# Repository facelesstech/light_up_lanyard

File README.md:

# light_up_lanyard
light_up_lanyard

Blog post - https://facelesstech.wordpress.com/2023/03/04/light-up-paracord-lanyard/

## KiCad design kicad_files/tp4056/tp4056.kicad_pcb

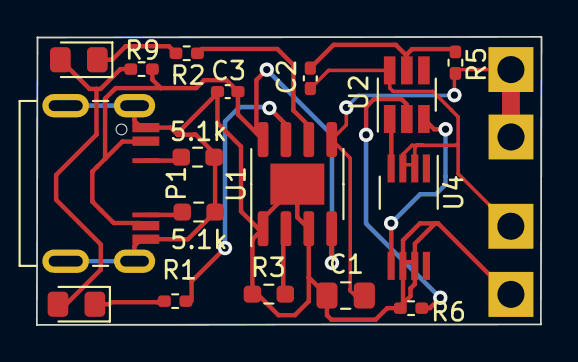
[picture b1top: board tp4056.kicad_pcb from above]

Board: 2 copper layers, 28.0 x 16.0 mm, 21 parts (0 on the bottom side), 16 nets.

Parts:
C1: 10uF; C_0805_2012Metric_Pad1.18x1.45mm_HandSolder
C2, C3: 0.1uF; C_0402_1005Metric_Pad0.74x0.62mm_HandSolder
D1: RED; LED_0805_2012Metric_Pad1.15x1.40mm_HandSolder
D2: GREEN; LED_0805_2012Metric_Pad1.15x1.40mm_HandSolder
J4, J5, J6, J7: Conn_01x01_Female; 1.5mm_test_point
P1: USB_C_Plug; USB_C_Receptacle_JAE_DX07S016JA1R1500
R1, R2: 1k; R_0402_1005Metric_Pad0.72x0.64mm_HandSolder
R3: 10k; R_0603_1608Metric_Pad0.98x0.95mm_HandSolder
R5: 100; R_0402_1005Metric_Pad0.72x0.64mm_HandSolder
R6: 0R; R_0402_1005Metric_Pad0.72x0.64mm_HandSolder
R7, R8: 5.1k; R_0603_1608Metric_Pad0.98x0.95mm_HandSolder
R9: R; R_0402_1005Metric_Pad0.72x0.64mm_HandSolder
U1: TP4056; SOIC-8-1EP_3.9x4.9mm_P1.27mm_EP2.29x3mm
U2: DW01; SOT-23-6_Handsoldering
U4: 8205a; SOT-23-8_Handsoldering_long

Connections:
/G1: U2.1 (OD), U4.4 (G)
/OC: R6.1, U2.2 (CS)
BAT+: C1.1, J6.1, J7.1, R5.1, U1.5 (BAT)
BAT-: C2.2, J4.1, U2.6 (GND), U4.2 (S), U4.3 (S)
GND: C1.2, C3.2, J5.1, P1.A1 (GND), P1.A12 (GND), P1.S1 (SHIELD), R3.2, R6.2, R7.2, R8.2, U1.1 (TEMP), U1.3 (GND), U1.9 (PP), U4.6 (S), U4.7 (S)
unnamed: C2.1, R5.2, U2.5 (VCC)
unnamed: D1.1 (K), R1.1
unnamed: D1.2 (A), D2.2 (A), R9.2
unnamed: D2.1 (K), R2.1
unnamed: P1.A8 (SBU1), R8.1
unnamed: P1.B8 (SBU2), R7.1
unnamed: R1.2, U1.7 (~CHRG)
unnamed: R2.2, U1.6 (~STDBY)
unnamed: R3.1, U1.2 (PROG)
unnamed: U2.3 (OC), U4.5 (G)
VIN: C3.1, P1.A4 (VBUS), P1.A9 (VBUS), R9.1, U1.4 (VCC), U1.8 (CE)

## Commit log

2023-03-04 3d print files
2023-03-04 kicad files
2023-03-04 added photo
2023-03-04 added photo to readme
2023-03-04 added blog link to readme
